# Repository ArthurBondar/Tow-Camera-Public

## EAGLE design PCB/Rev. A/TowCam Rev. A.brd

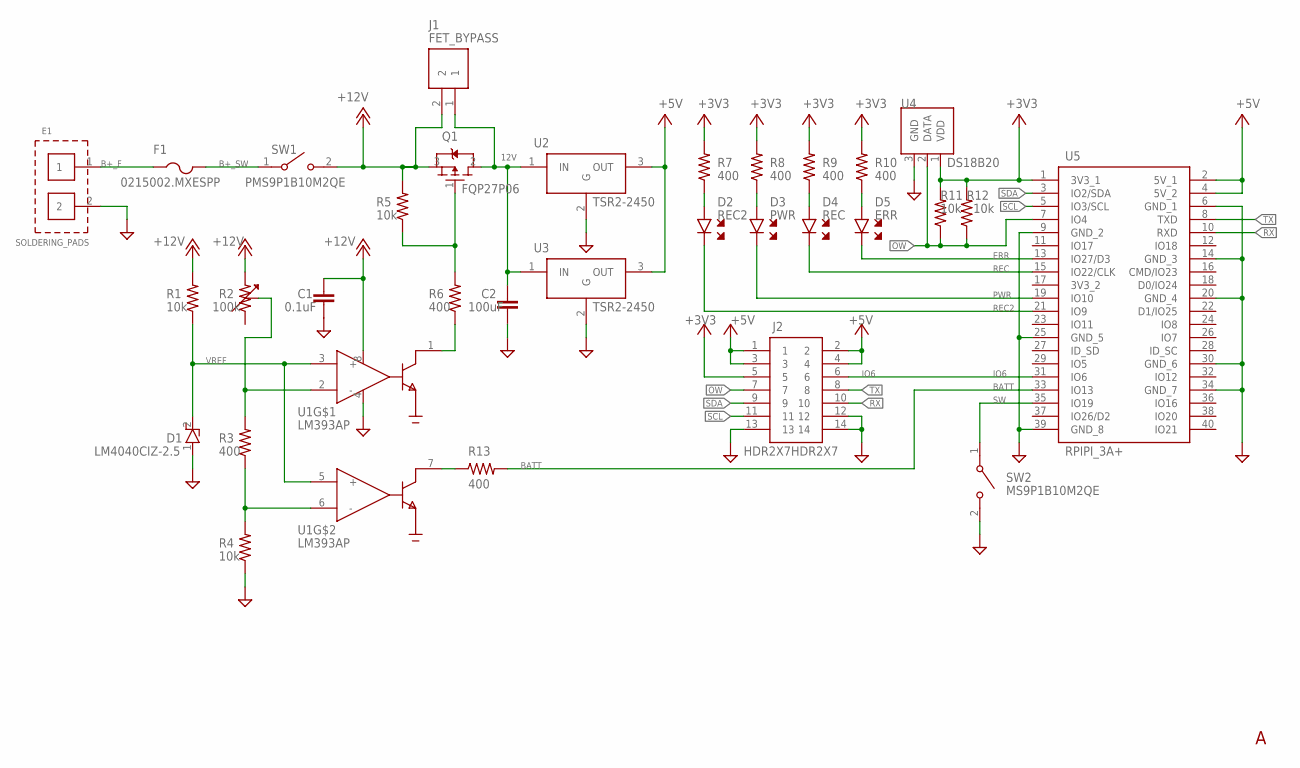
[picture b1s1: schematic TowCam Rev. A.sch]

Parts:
C1: 0.1uF; CAPPRD254W65D300H300B
C2: 100uF; CAP-TH-5MM
D1: LM4040CIZ-2.5; TO-92
D2: REC2; LEDRD254W60D565H860B
D3: PWR; R0805
D4: REC; R0805
D5: ERR; R0805
E1: SOLDERING_PADS
F1: 0215002.MXESPP
J1: FET_BYPASS; HDR1X2
J2: HDR2X7HDR2X7; HDR2X7
Q1: FQP27P06; TO-220-BEND
R1, R4, R5, R11, R12: 10k; R0805
R2: 100k; PV36W104C01B00
R3, R6, R7, R8, R9, R10, R13: 400; R0805
SW1: PMS9P1B10M2QE
SW2: MS9P1B10M2QE; PMS9P1B10M2QE
U1: LM393AP; DIP8
U2, U3: TSR2-2450
U4: DS18B20; TO-92
U5: RPIPI_3A+; PI_3A+

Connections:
12V: C2.1, J1.1, Q1.2 (D), U2.1 (IN), U3.1 (IN)
+3V3: J2.5, R7.2, R8.2, R9.2, R10.2, R11.2, R12.2, U4.1 (VDD), U5.1 (3V3_1)
+5V: J2.1, J2.2, J2.3, J2.4, U2.3 (OUT), U3.3 (OUT), U5.2 (5V_1), U5.4 (5V_2)
+12V: C1.1, J1.2, Q1.3 (S), R1.2, R2.3, R5.2, SW1.2, U1.8 (VCC)
B+_F: E1.1, F1.1
B+_SW: F1.2, SW1.1
BATT: R13.2, U5.33 (IO13)
ERR: D5.2, U5.13 (IO27/D3)
GATE: Q1.1 (G), R5.1, R6.2
GND: C1.2, C2.2, D1.1 (A), E1.2, J2.12, J2.13, J2.14, R4.1, SW2.2, U1.4 (GND), U2.2 (G), U3.2 (G), U4.3 (GND), U5.6 (GND_1), U5.9 (GND_2), U5.14 (GND_3), U5.20 (GND_4), U5.25 (GND_5), U5.30 (GND_6), U5.34 (GND_7), U5.39 (GND_8)
IO6: J2.6, U5.31 (IO6)
unnamed: R13.1, U1.7 (OUT)
unnamed: R2.2, R3.2, U1.2 (-)
unnamed: R3.1, R4.2, U1.6 (-)
unnamed: D2.1, R7.1
unnamed: R6.1, U1.1 (OUT)
unnamed: D3.1, R8.1
unnamed: D4.1, R9.1
unnamed: D5.1, R10.1
OW: J2.7, R11.1, R12.1, U4.2 (DATA), U5.7 (IO4)
PWR: D3.2, U5.19 (IO10)
REC: D4.2, U5.15 (IO22/CLK)
REC2: D2.2, U5.21 (IO9)
RX: J2.10, U5.10 (RXD)
SCL: J2.11, U5.5 (IO3/SCL)
SDA: J2.9, U5.3 (IO2/SDA)
SW: SW2.1, U5.35 (IO19)
TX: J2.8, U5.8 (TXD)
VREF: D1.2 (C), R1.1, U1.3 (+), U1.5 (+)

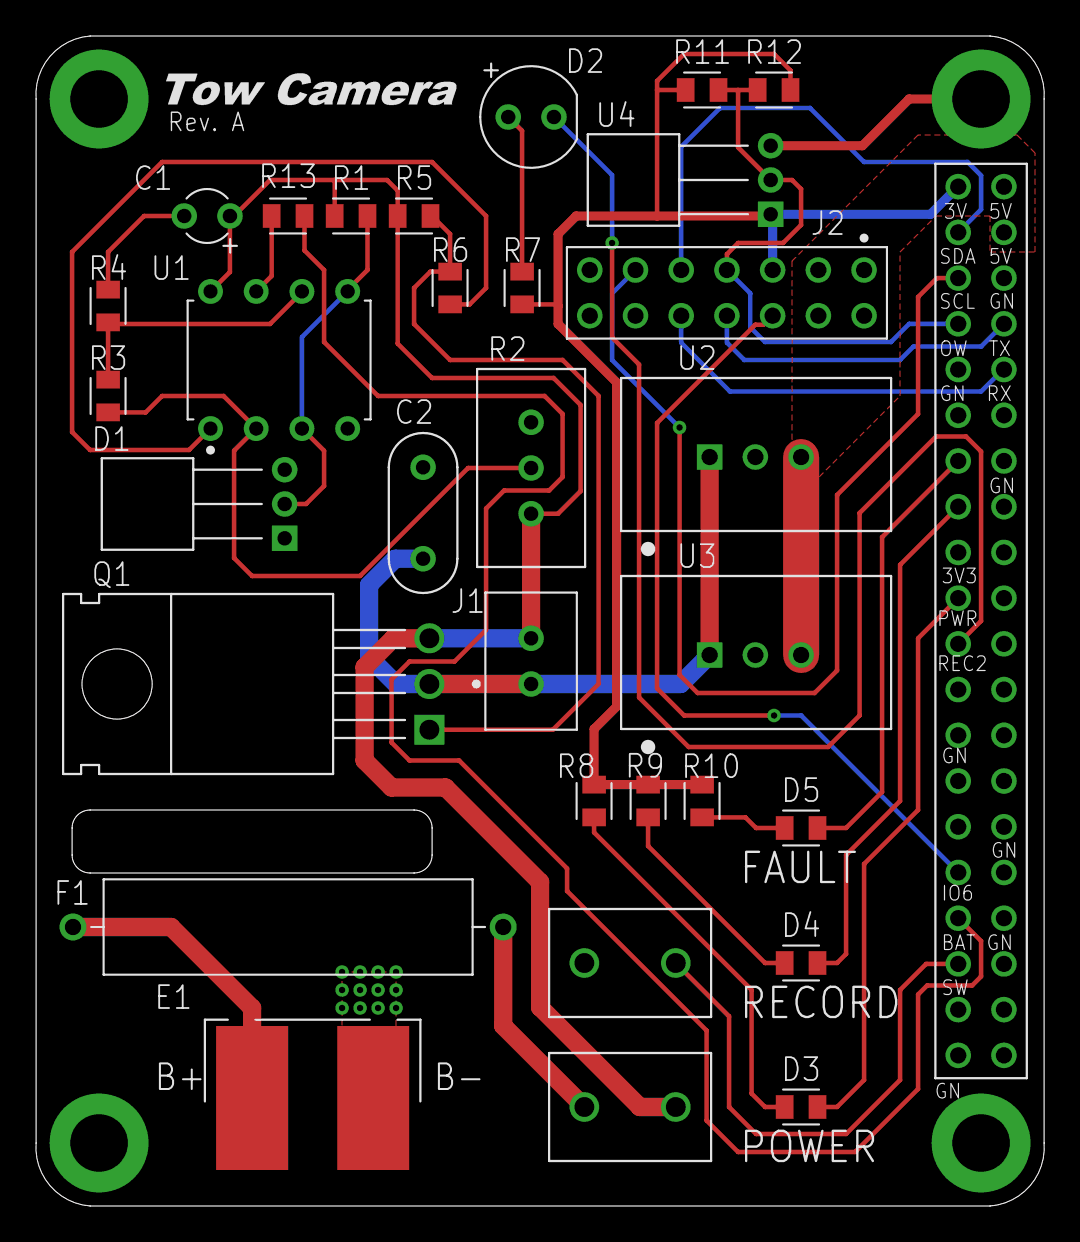
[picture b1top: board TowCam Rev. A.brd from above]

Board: 2 copper layers, 56.0 x 65.0 mm, 32 parts (0 on the bottom side), 29 nets.

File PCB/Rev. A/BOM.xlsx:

Qty | Part Number | Ref. Designator | Value | Package | Description
1 | CAPACITORRAD-3MM | C1 | 0.1uF | CAPPRD254W65D300H300B | Capacitor
1 | FUSE0215002.MXESPP | F1 | 0215002.MXESPP | 0215002.MXESPP | Fuse - Various Devices
1 | PV36W104C01B00 | R2 | 100k | PV36W104C01B00 | PV36W104C01B00 Bourns Inc.
1 | CAP_THCAP-TH-5MM | C2 | 100uF | CAP-TH-5MM | Capacitor Electro. TH
5 | RESISTOR0805 | R1, R4, R5, R11, R12 | 10k | R0805 | Resistor US
7 | RESISTOR0805 | R3, R6, R7, R8, R9, R10, R13 | 400 | R0805 | Resistor US
1 | DS18B20 | U4 | DS18B20 | TO-92 | DS18B20+T&R Maxim Integrated
1 | LED0805 | D5 | ERR | R0805 | LED GENERIC
1 | HDR1X22P2.54MM | J1 | FET_BYPASS | HDR1X2 | Header 2pin 2.54mm pitch
1 | FQP27P06 | Q1 | FQP27P06 | TO-220-BEND | FQP27P06 ON Semiconductor
1 | HDR2X7HDR2X7 | J2 | HDR2X7HDR2X7 | HDR2X7
1 | LM393APDIP8 | U1 | LM393AP | DIP8 | LM393AP Texas Instruments
1 | ZENERLM4040CIZ-2.5 | D1 | LM4040CIZ-2.5 | TO-92 | Voltage Reference - Zener Diode
2 | SPSTPMS9P1B10M2QE | SW1, SW2 | PMS9P1B10M2QE | PMS9P1B10M2QE | Switch SPST
1 | LED0805 | D3 | PWR | R0805 | LED GENERIC
1 | LED0805 | D4 | REC | R0805 | LED GENERIC
1 | LED_THLED-2.54 | D2 | REC2 | LEDRD254W60D565H860B | TH LED - large
1 | RPIPI_3A+ | U5 | RPIPI_3A+ | PI_3A+ | Pi Header with different package variations
1 | SOLDERING_PADS | E1 | SOLDERING_PADS | SOLDERING_PADS | Pads for soldering wires
2 | TSR2-2450 | U2, U3 | TSR2-2450 | TSR2-2450 | TSR 2-2450 Traco Power

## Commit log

2024-05-27 Making the project public, original files from July, 2020
